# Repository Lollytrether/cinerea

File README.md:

# cinerea
The project name was something I come up with on the spot 

Note the most of my time recorded on lapse has been on tinkercad
As for what I have been doing, I tried using Altium Designer (it's industry standard) and ultimately failed after trying to find
the specific esp32. I have had to rewire the PCB 3 times, first was sort of an "this is completely new", then I realised that half the wires couldn't reach because other wires were blocking. And after I finally got that done, I realised the USB port to connect the ESP-32 to my computer was poking out in the middle of the PCB. So I had to rotate that and rewire it again. Then when it came to the 3d models, the keys and the ESP32 were missing, aligning them took an hour or so. 

Note:
Start the BOM 
Finish the modelling
Update READme

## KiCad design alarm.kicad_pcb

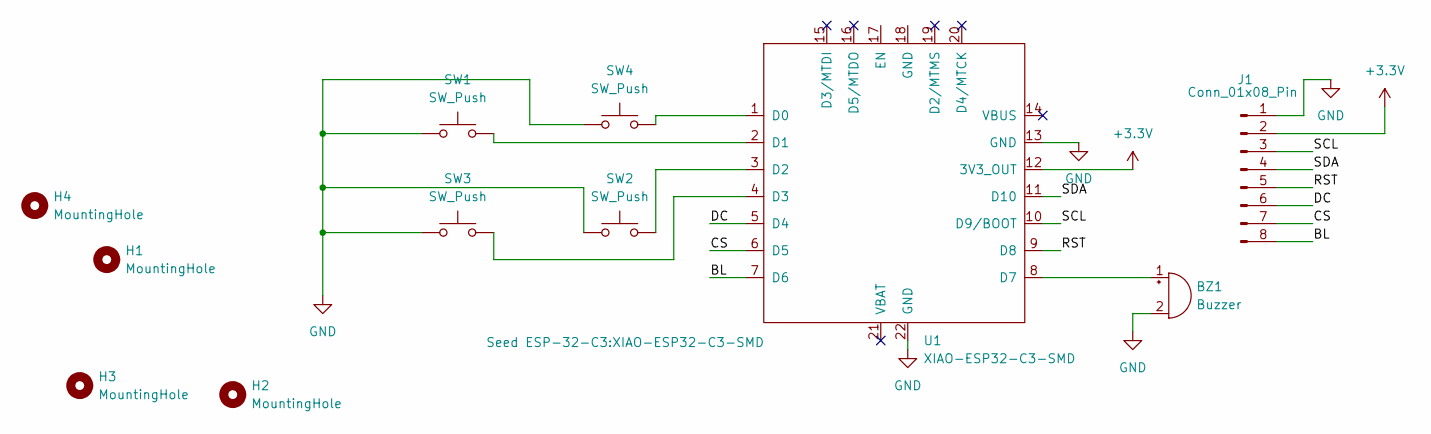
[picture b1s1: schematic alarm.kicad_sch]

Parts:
BZ1: Buzzer; Buzzer_12x9.5RM7.6
H1, H2, H3, H4: MountingHole; MountingHole_2.1mm
J1: Conn_01x08_Pin; PinHeader_1x08_P2.54mm_Vertical
SW1, SW2, SW3, SW4: SW_Push; SW_Cherry_MX_1.00u_PCB
U1: XIAO-ESP32-C3-SMD

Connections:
+3.3V: J1.2, U1.12 (3V3_OUT)
/BL: J1.8, U1.7 (D6)
/CS: J1.7, U1.6 (D5)
/DC: J1.6, U1.5 (D4)
/RST: J1.5, U1.9 (D8)
/SCL: J1.3, U1.10 (D9/BOOT)
/SDA: J1.4, U1.11 (D10)
GND: BZ1.2 (-), J1.1, SW1.1, SW2.1, SW3.1, SW4.1, U1.13 (GND), U1.22 (GND)
unnamed: BZ1.1 (+), U1.8 (D7)
unnamed: SW4.2, U1.1 (D0)
unnamed: SW1.2, U1.2 (D1)
unnamed: SW2.2, U1.3 (D2)
unnamed: SW3.2, U1.4 (D3)

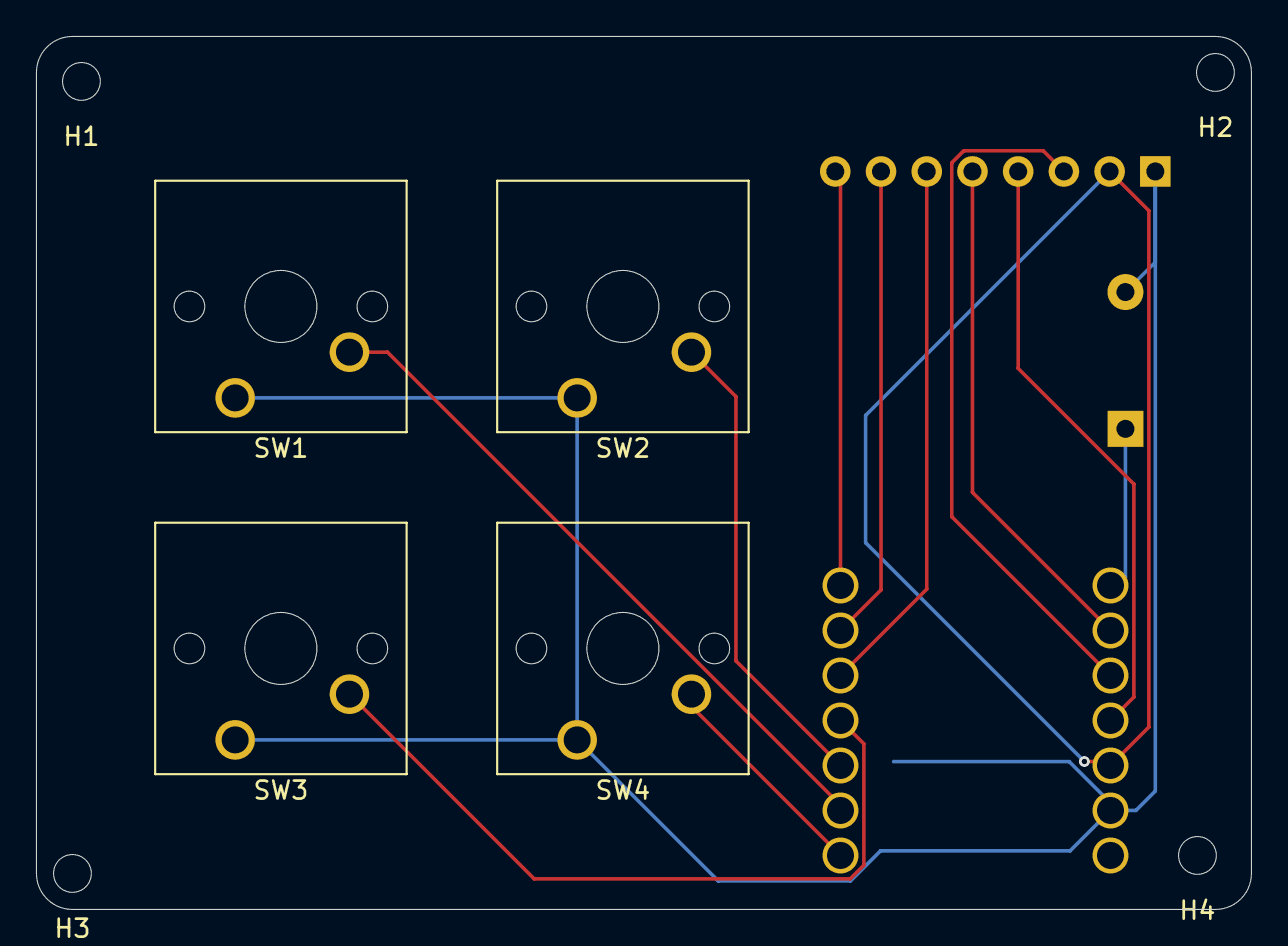
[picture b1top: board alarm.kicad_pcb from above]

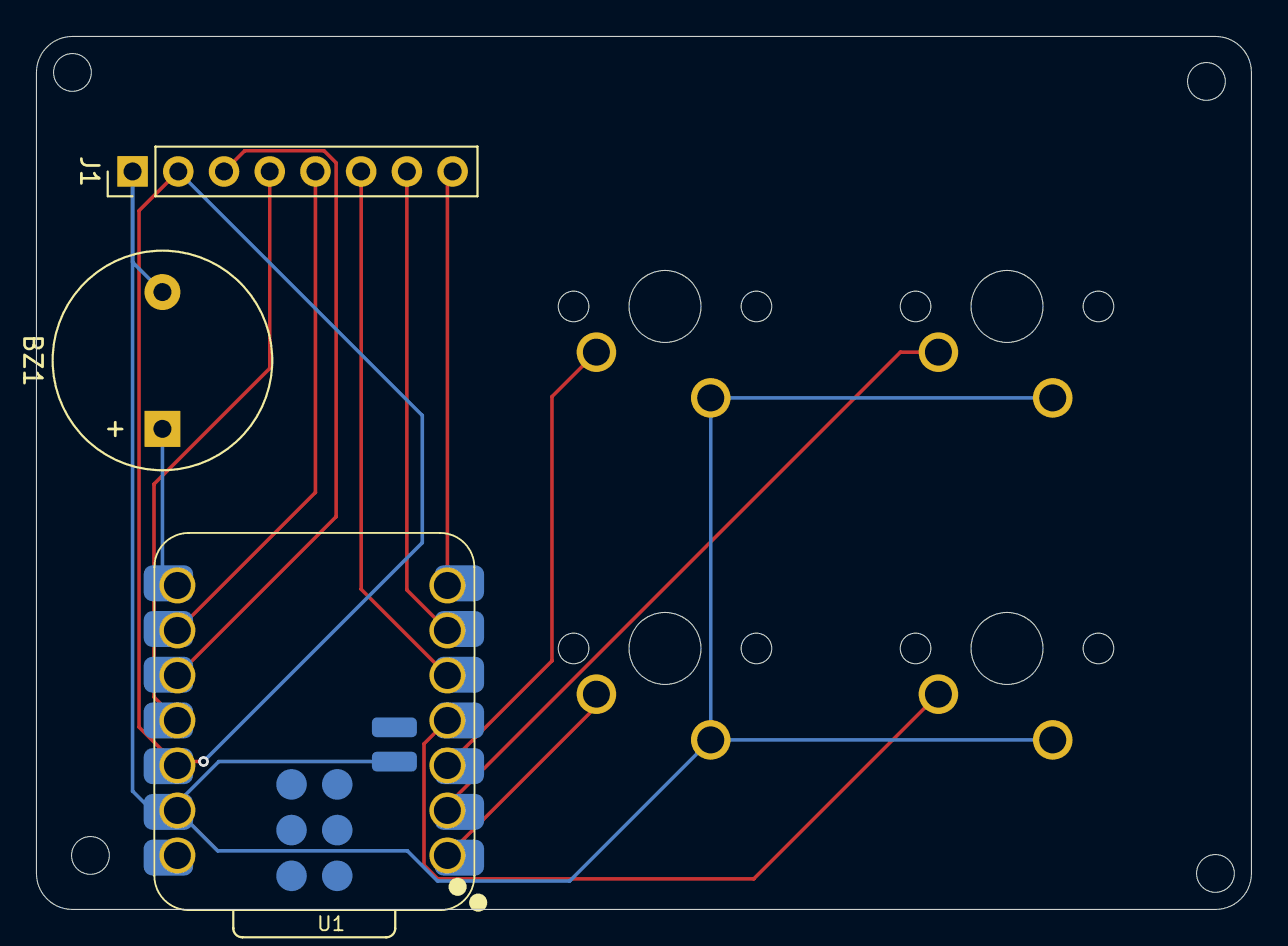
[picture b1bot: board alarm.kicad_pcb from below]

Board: 2 copper layers, 67.5 x 48.5 mm, 11 parts (3 on the bottom side), 13 nets.
